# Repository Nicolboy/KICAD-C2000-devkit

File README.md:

# KICAD-C2000-devkit

- **56/56** — connector pins identical between the F280037 and F28P551
  devkits, fully interchangeable on the same shield
- **100% generated** — pin spec lives in Markdown, not in KiCad; a script
  derives the symbols and schematics from it, so GPIO/pin uniqueness and
  measurement-trace grounding are enforced rules, not just documentation
- Devkit B PCB **routed 100% on 4 layers**, DRC clean

Carrier boards for a TMS320 C2000 digital power-converter controller,
supervised by an ESP32-C6 for Wi-Fi and FOTA updates, designed in KiCad 10.

Shield d'isolation et cartes devkit pour TMS320 C2000, conçus sous KiCad 10.
Le brochage est décrit en Markdown, les symboles et les projets KiCad en sont
**générés** — le document reste la source de vérité, pas le schéma.

Cible : une commande numérique de convertisseur de puissance isolé, pilotée par
un C2000 et supervisée par un ESP32-C6 pour le Wi-Fi et la mise à jour FOTA.

---

## Architecture — quatre cartes, une barrière

| Carte | Rôle |
|---|---|
| **Puissance** | Conversion, barrière d'isolation, isolateurs (AMC0311S, AMC0300R, ISO7710, DPC817), shunts en connexion Kelvin, régulateurs |
| **Shield** | Support mécanique des deux devkits, adaptation de brochage, conditionnement analogique, protections. **Aucun composant isolé** |
| **Devkit C2000** | MCU, deux LDO 3,3 V, JTAG, bouton reset, LED, cavalier de boot |
| **Devkit ESP32** | Wi-Fi, hôte FOTA, écran OLED en SPI |

L'isolation est entièrement confinée à la carte de puissance. Le shield ne fait
que du conditionnement côté froid : c'est ce qui permet de le fabriquer en
2 couches à la maison sans se poser de question de ligne de fuite.

Liaison shield ↔ puissance : quatre nappes 2 × 8 à **alternance signal / masse
stricte 1:1**, aucune alimentation dedans. Le +5 V passe par un connecteur
séparé — les 500 mA de la commande n'ont pas à partager leur retour avec les
masses de référence des voies ADC.

---

## Le point de conception le plus notable

**Le connecteur est identique à 100 % entre le F280037 et le F28P551**, 56
positions sur 56. Les deux devkits sont interchangeables sur le shield.

Ce n'est pas une coïncidence, c'est le résultat d'un arbitrage : les LED ont été
délibérément posées sur les **entrées/sorties non communes** aux deux boîtiers,
pour que toutes les broches qui traversent le connecteur, elles, soient
communes.

---

## Le brochage est du code

Le fichier [`doc/spec-devkit.md`](doc/spec-devkit.md) fait autorité. Les
symboles KiCad, les schémas et les vérifications en découlent par génération —
on ne modifie jamais un `.kicad_sym` à la main.

```
doc/spec-devkit.md            source de vérité, relue par un humain
        │
        ├── gen_symbole_mcu.py   → build/C2000_MCU_LQFP64.kicad_sym
        │                          (dimensionne le symbole depuis les noms)
        │
        └── gen_devkit.py        → devkit_A_F280037.*  devkit_B_F28P551.*
              ▲                    kicad_gen.py — primitives communes
              │
            src/*.kicad_sch        schémas source des devkits, versionnés

shield.*                       édité à la main dans KiCad — pas généré
```

L'intérêt n'est pas le gain de temps, c'est que **les règles de conception
deviennent exécutables**. Les générateurs vérifient ce que le document promet :
unicité des broches et des GPIO, masse de part et d'autre des voies de mesure de
courant, présence des réserves. Une divergence entre l'intention et le schéma
est une erreur de script, pas un oubli qu'on découvre au routage.

`gen_symbole_mcu.py` dimensionne par exemple le corps du symbole à partir de la
longueur réelle du nom de broche le plus long, pour que les textes des quatre
faces ne se croisent jamais — plutôt qu'une taille choisie à l'œil qui casse au
premier nom un peu long.

Les schémas ne contiennent d'ailleurs **aucun fil** : toute la connectivité
passe par des étiquettes globales posées sur le point de connexion de chaque
broche. C'est ce qui permet d'ajouter un composant par script sans rien router.

---

## Concevoir avec un agent

Une part inhabituelle du travail est faite par un agent : lire les datasheets,
en extraire les contraintes, écrire la spécification, générer les symboles,
poser les composants et choisir les boîtiers. **Le placement et le routage
restent manuels** — ils encodent des choix que rien ne devine sur une chaîne de
mesure de courant.

[`doc/methode-kicad-claude.md`](doc/methode-kicad-claude.md) documente cette
façon de travailler : le partage des rôles, le déroulé d'une séance, et surtout
les pièges de format rencontrés — chacun avec sa signature, parce que KiCad
répond « échec du chargement » et rien de plus quand un fichier est malformé.

---

## Projets KiCad

Trois, pas un de plus.

| Projet | Contenu |
|---|---|
| `shield.*` | Shield, connecteurs devkit 2 × 28, quatre nappes, ESP32-C6 |
| `devkit_A_F280037.*` | Devkit TMS320F280037CSPM |
| `devkit_B_F28P551.*` | Devkit TMS320F28P551SG5PM |

---

## Reproduire

KiCad 10 et Python 3.12 requis. `kicad-cli` doit être dans le `PATH`.

```bash
python gen_symbole_mcu.py -o build/     # symboles MCU
python gen_devkit.py --force            # les deux projets devkit

kicad-cli sch erc --exit-code-violations <projet>.kicad_sch
kicad-cli pcb drc --exit-code-violations <projet>.kicad_pcb
```

`shield.*` n'apparaît pas ici : il est édité à la main et ne se régénère pas.
Les schémas de devkit produits à la racine sont en revanche **jetables** — toute
retouche manuelle y est perdue au prochain `--force`. Ce qui doit survivre se
modifie dans `src/` ou dans le générateur.

Chaque carte existe en **deux versions de fabrication** : 2 couches gravées à
la maison — pistes 1 mm, vias 2 mm, perçage 0,8 mm — pour itérer vite sur la
mécanique, et 4 couches en fabrication externe, avec plan de masse continu sous
la zone analogique. Même schéma, même brochage, seul le PCB change.

---

## État d'avancement

Travail en cours, et le dire plutôt que de le masquer :

- **Devkit B (F28P551)** — **PCB routé à 100 %** (24 empreintes, DRC à 0
  violation). Les deux connecteurs 2 × 28 portent désormais une sérigraphie
  par broche — canal ADC réel, GPIO, rôle de bus générique (`I2C_CK`/`DT`,
  `SPI_CK`/`DO`/`DI`/`CS`...) et alimentations, plutôt que les noms
  spécialisés du schéma (`Vin`, `I_SHUNT1_CMP`...), pour que le connecteur se
  lise seul. L'ERC du schéma reste à 41 violations, de la même famille que
  les autres projets (pins de réserve non pilotées).
- **Devkit A (F280037)** — PCB **peuplé** (27 empreintes posées depuis le
  schéma) mais pas encore routé : 106 pastilles non connectées au DRC.
- **Shield** — connecteurs posés, alimentations câblées avec `PWR_FLAG` par
  net. Le routage des signaux n'est pas fait : il demande des choix de
  conception qui n'ont pas leur place dans un générateur. D'où les 108
  violations d'ERC (`pin_not_connected` attendus). PCB non routé.
- **Carte de puissance** — spécifiée dans `doc/`, pas encore dessinée.

Les points laissés ouverts — caractéristiques de sortie des AMC, courant
d'entrée du REFIN, choix de VREFHI — sont listés en fin de
[`doc/decisions.md`](doc/decisions.md). Ils attendent une lecture de datasheet,
pas une estimation.

---

## Décisions à ne pas défaire

Certains choix ressemblent à des inefficacités sans en être. Les treize sont
documentés dans [`doc/decisions.md`](doc/decisions.md), chacun avec sa raison et
ce qui casse si on le défait — entre autres :

- Les **PWM3 et PWM4 restent en réserve et restent des PWM** : ce sont les deux
  seules paires complémentaires HRPWM avec temps mort matériel disponibles.
- Chaque shunt sort **deux fois**, `_MES` filtré et `_CMP` direct. Le chemin
  comparateur attaque le CMPSS sans filtre anti-repliement : pas de retard sur
  le déclenchement de la Trip Zone, et un défaut du filtre ne désarme pas la
  protection.
- Les **16 voies ADC sortent toutes** pour 9 nécessaires, les 5 libres étant
  câblées jusqu'aux réserves de nappe. Une voie ajoutée plus tard se raccorde
  sans retoucher une seule carte.

---

## Licence

[CERN-OHL-S v2](LICENSE) — CERN Open Hardware Licence, fortement réciproque.

Tu peux étudier, modifier, fabriquer et distribuer ce matériel. En contrepartie,
si tu distribues un produit fondé dessus, ou une version modifiée, tu dois
publier les sources correspondantes sous la même licence.

C'est la licence de référence du matériel libre, l'équivalent de la GPL côté
logiciel. Si tu préfères une réciprocité limitée à la carte elle-même, ou pas de
réciprocité du tout, les variantes CERN-OHL-W et CERN-OHL-P existent.

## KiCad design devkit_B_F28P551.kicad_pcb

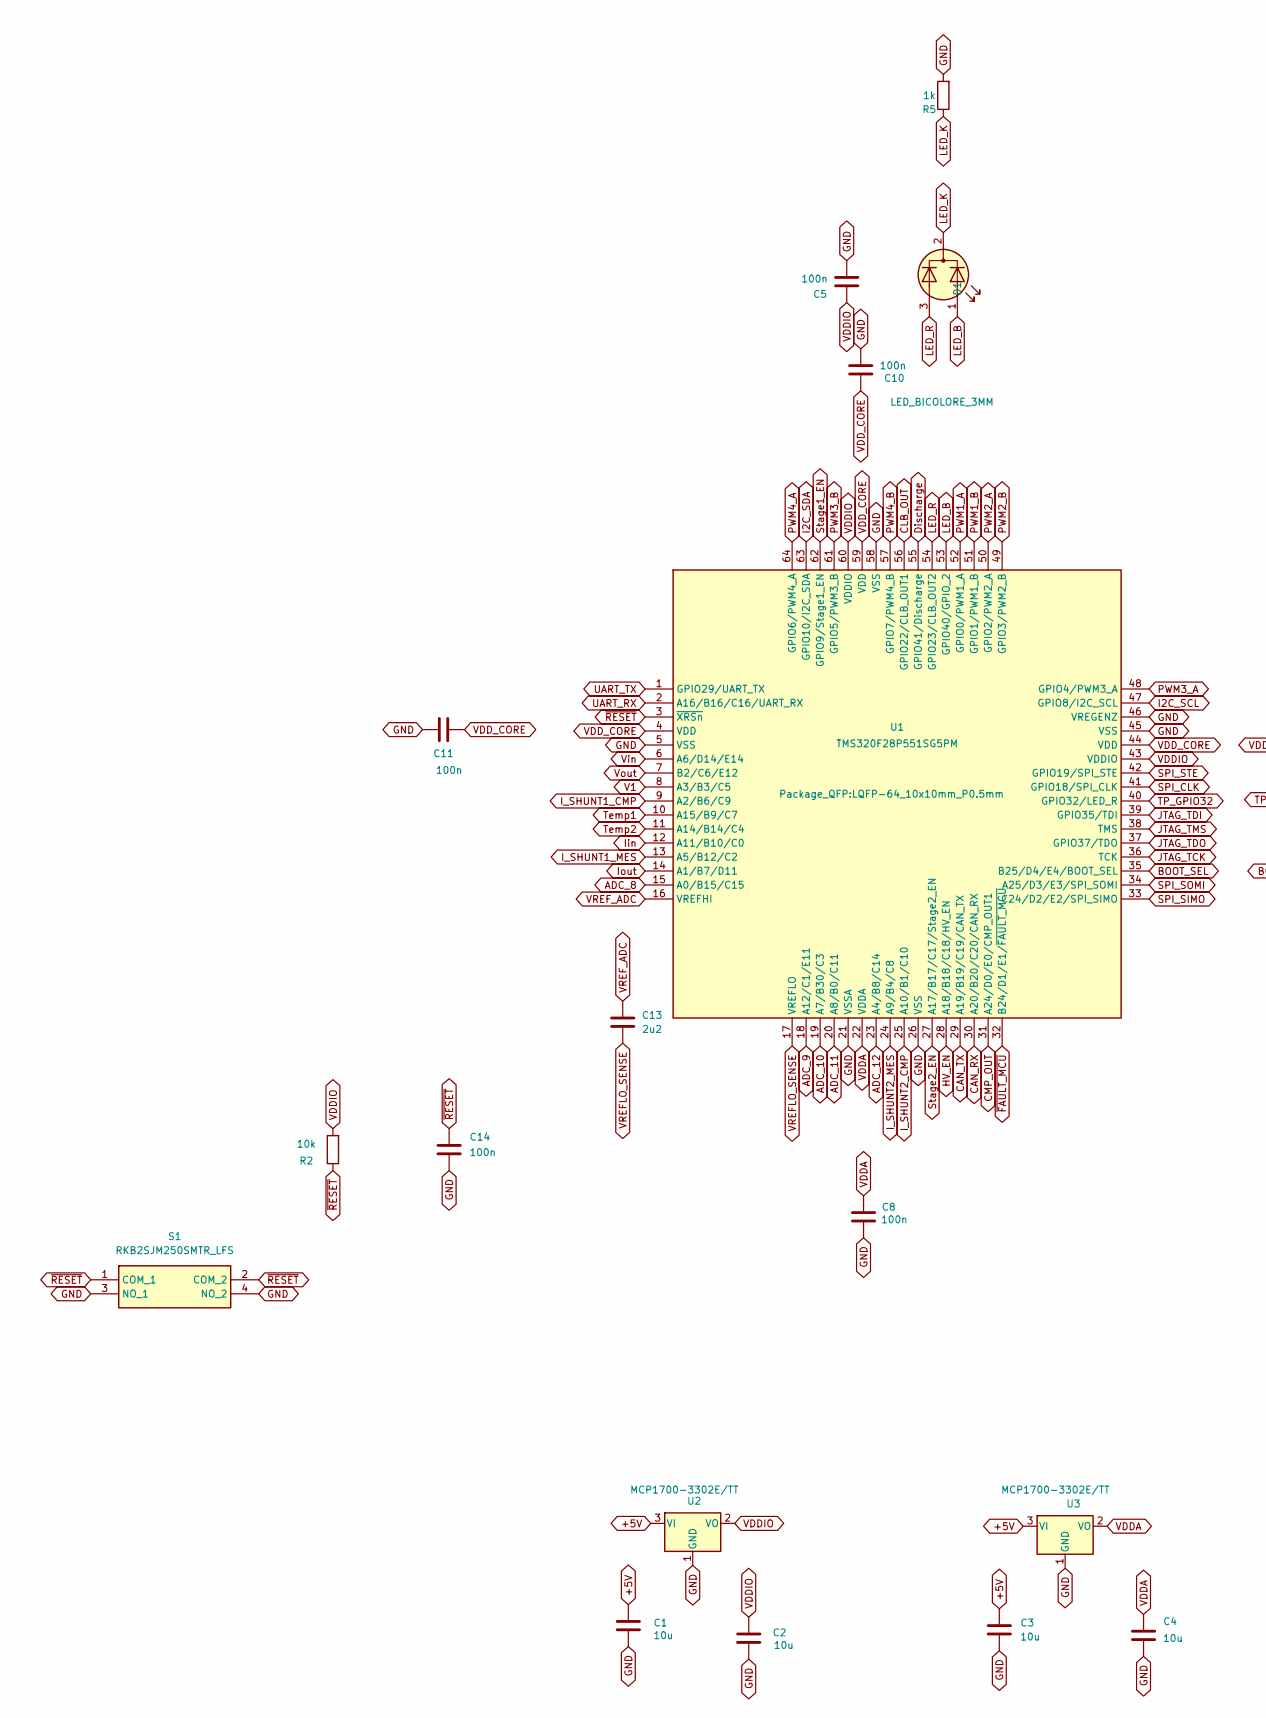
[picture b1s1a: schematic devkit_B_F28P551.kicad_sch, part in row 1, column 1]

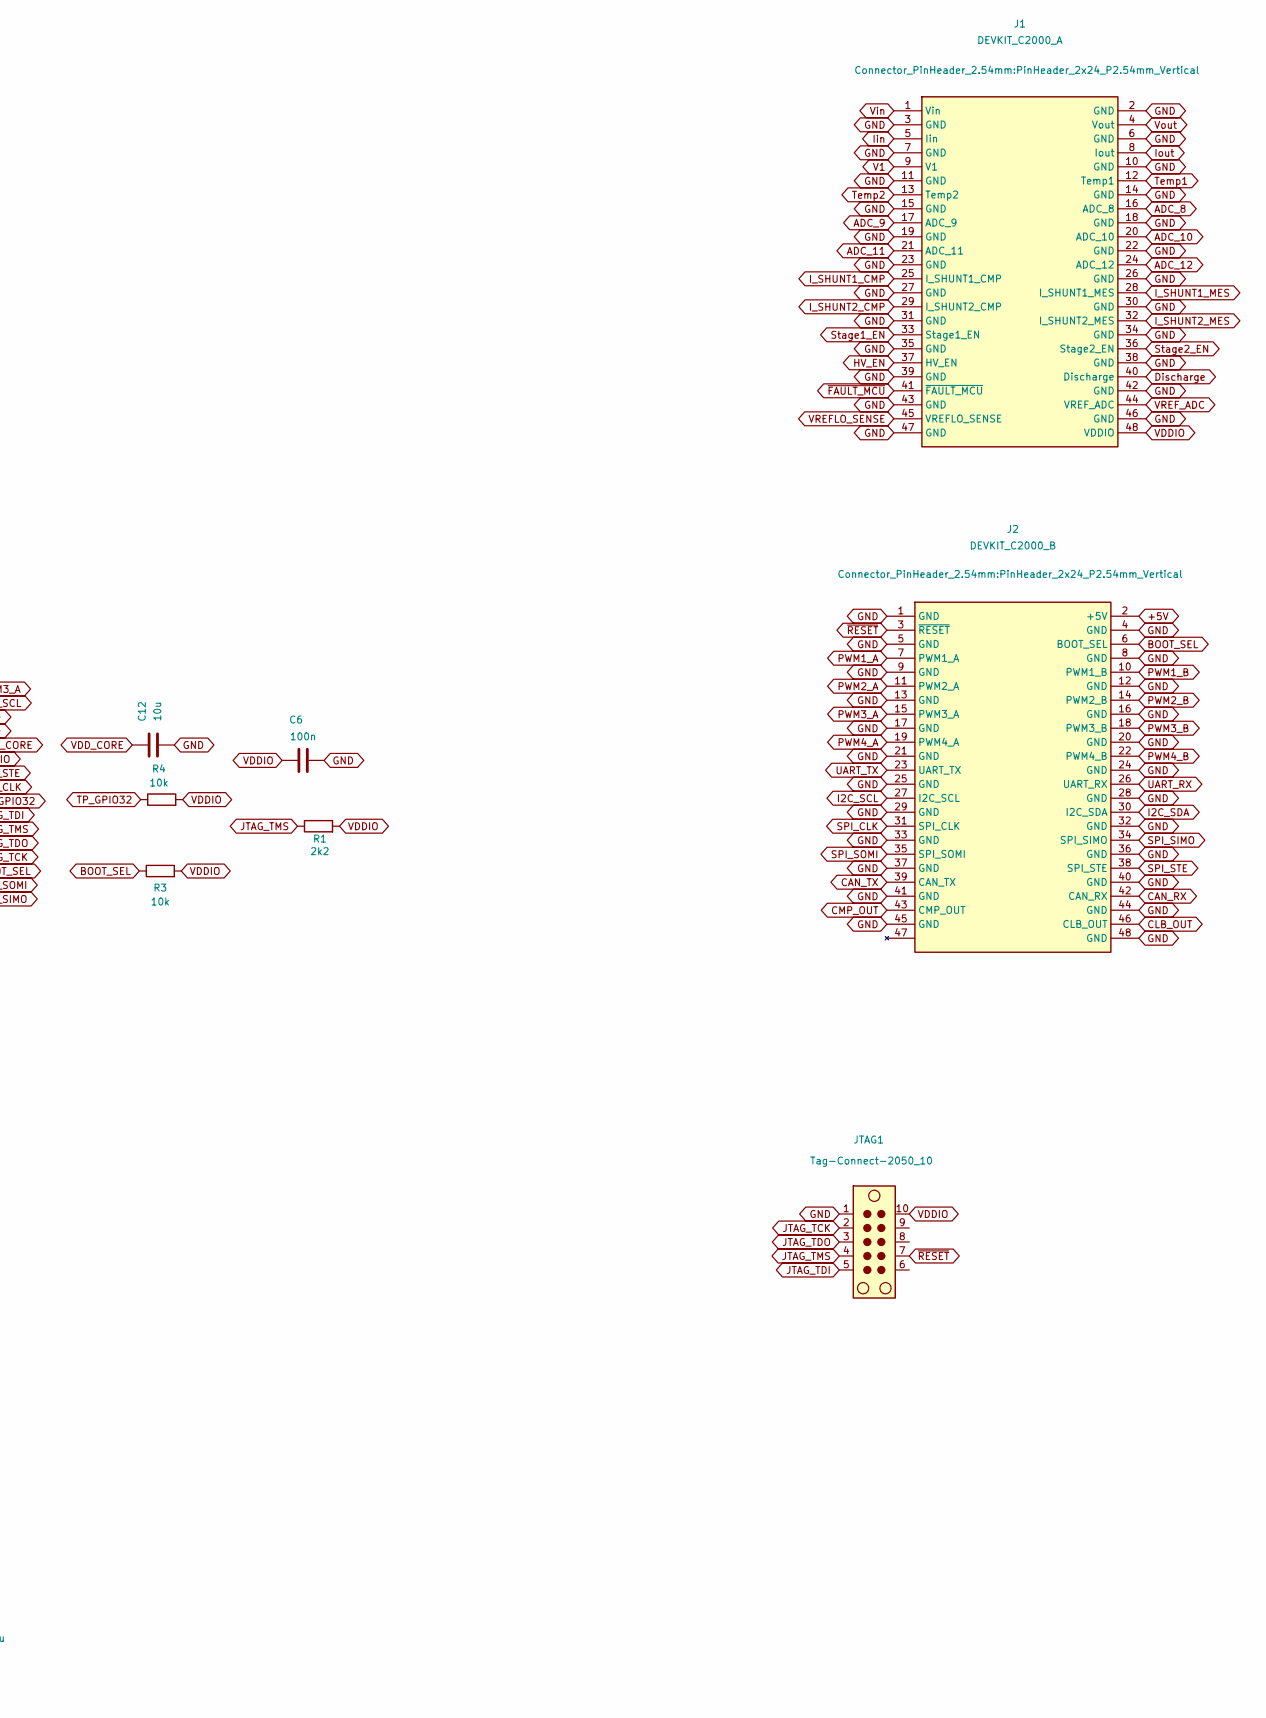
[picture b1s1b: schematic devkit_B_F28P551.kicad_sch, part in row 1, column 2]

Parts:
C1, C2, C3, C4, C12: 10u; C_0805_2012Metric
C5, C6, C8, C10, C11, C14: 100n; C_0805_2012Metric
C13: 2u2; C_0805_2012Metric
D1: LED_BICOLORE_3MM; LED_D3.0mm-3
J1: DEVKIT_C2000_A; PinHeader_2x24_P2.54mm_Vertical
J2: DEVKIT_C2000_B; PinHeader_2x24_P2.54mm_Vertical
JTAG1: Tag-Connect-2050_10; Tag-Connect_TC2050-IDC-NL_2x05_P1.27mm_Vertical
R1: 2k2; R_0805_2012Metric
R2, R3, R4: 10k; R_0805_2012Metric
R5: 1k; R_0805_2012Metric
S1: RKB2SJM250SMTR_LFS; RKB2SJM250SMTRLFS; Mouser Part Number 611-RKB2SJM250SMTRLF
U1: TMS320F28P551SG5PM; LQFP-64_10x10mm_P0.5mm
U2, U3: MCP1700-3302E/TT; SOT-23

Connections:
+5V: C1.1, C3.1, J2.2 (+5V), U2.3 (VI), U3.3 (VI)
ADC_8: J1.16 (ADC_8), U1.15 (A0/B15/C15)
ADC_9: J1.17 (ADC_9), U1.18 (A12/C1/E11)
ADC_10: J1.20 (ADC_10), U1.19 (A7/B30/C3)
ADC_11: J1.21 (ADC_11), U1.20 (A8/B0/C11)
ADC_12: J1.24 (ADC_12), U1.23 (A4/B8/C14)
BOOT_SEL: J2.6 (BOOT_SEL), R3.1, U1.35 (B25/D4/E4/BOOT_SEL)
CAN_RX: J2.42 (CAN_RX), U1.30 (A20/B20/C20/CAN_RX)
CAN_TX: J2.39 (CAN_TX), U1.29 (A19/B19/C19/CAN_TX)
CLB_OUT: J2.46 (CLB_OUT), U1.56 (GPIO22/CLB_OUT1)
CMP_OUT: J2.43 (CMP_OUT), U1.31 (A24/D0/E0/CMP_OUT1)
Discharge: J1.40 (Discharge), U1.55 (GPIO41/Discharge)
GND: C1.2, C2.2, C3.2, C4.2, C5.2, C6.2, C8.2, C10.2, C11.2, C12.2, C14.2, J1.2 (GND), J1.3 (GND), J1.6 (GND), J1.7 (GND), J1.10 (GND), J1.11 (GND), J1.14 (GND), J1.15 (GND), J1.18 (GND), J1.19 (GND), J1.22 (GND), J1.23 (GND), J1.26 (GND), J1.27 (GND), J1.30 (GND), J1.31 (GND), J1.34 (GND), J1.35 (GND), J1.38 (GND), J1.39 (GND), J1.42 (GND), J1.43 (GND), J1.46 (GND), J1.47 (GND), J2.1 (GND), J2.4 (GND), J2.5 (GND), J2.8 (GND), J2.9 (GND), J2.12 (GND), J2.13 (GND), J2.16 (GND), J2.17 (GND), J2.20 (GND), J2.21 (GND), J2.24 (GND), J2.25 (GND), J2.28 (GND), J2.29 (GND), J2.32 (GND), J2.33 (GND), J2.36 (GND), J2.37 (GND), J2.40 (GND), J2.41 (GND), J2.44 (GND), J2.45 (GND), J2.48 (GND), JTAG1.1, R5.2, S1.3 (NO_1), S1.4 (NO_2), U1.5 (VSS), U1.21 (VSSA), U1.26 (VSS), U1.45 (VSS), U1.46 (VREGENZ), U1.58 (VSS), U2.1 (GND), U3.1 (GND)
HV_EN: J1.37 (HV_EN), U1.28 (A18/B18/C18/HV_EN)
I2C_SCL: J2.27 (I2C_SCL), U1.47 (GPIO8/I2C_SCL)
I2C_SDA: J2.30 (I2C_SDA), U1.63 (GPIO10/I2C_SDA)
I_SHUNT1_CMP: J1.25 (I_SHUNT1_CMP), U1.9 (A2/B6/C9)
I_SHUNT1_MES: J1.28 (I_SHUNT1_MES), U1.13 (A5/B12/C2)
I_SHUNT2_CMP: J1.29 (I_SHUNT2_CMP), U1.25 (A10/B1/C10)
I_SHUNT2_MES: J1.32 (I_SHUNT2_MES), U1.24 (A9/B4/C8)
Iin: J1.5 (Iin), U1.12 (A11/B10/C0)
Iout: J1.8 (Iout), U1.14 (A1/B7/D11)
JTAG_TCK: JTAG1.2, U1.36 (TCK)
JTAG_TDI: JTAG1.5, U1.39 (GPIO35/TDI)
JTAG_TDO: JTAG1.3, U1.37 (GPIO37/TDO)
JTAG_TMS: JTAG1.4, R1.1, U1.38 (TMS)
LED_B: D1.1 (A1), U1.53 (GPIO40/GPIO_2)
LED_K: D1.2 (K), R5.1
LED_R: D1.3 (A2), U1.54 (GPIO23/CLB_OUT2)
PWM1_A: J2.7 (PWM1_A), U1.52 (GPIO0/PWM1_A)
PWM1_B: J2.10 (PWM1_B), U1.51 (GPIO1/PWM1_B)
PWM2_A: J2.11 (PWM2_A), U1.50 (GPIO2/PWM2_A)
PWM2_B: J2.14 (PWM2_B), U1.49 (GPIO3/PWM2_B)
PWM3_A: J2.15 (PWM3_A), U1.48 (GPIO4/PWM3_A)
PWM3_B: J2.18 (PWM3_B), U1.61 (GPIO5/PWM3_B)
PWM4_A: J2.19 (PWM4_A), U1.64 (GPIO6/PWM4_A)
PWM4_B: J2.22 (PWM4_B), U1.57 (GPIO7/PWM4_B)
SPI_CLK: J2.31 (SPI_CLK), U1.41 (GPIO18/SPI_CLK)
SPI_SIMO: J2.34 (SPI_SIMO), U1.33 (C24/D2/E2/SPI_SIMO)
SPI_SOMI: J2.35 (SPI_SOMI), U1.34 (A25/D3/E3/SPI_SOMI)
SPI_STE: J2.38 (SPI_STE), U1.42 (GPIO19/SPI_STE)
Stage1_EN: J1.33 (Stage1_EN), U1.62 (GPIO9/Stage1_EN)
Stage2_EN: J1.36 (Stage2_EN), U1.27 (A17/B17/C17/Stage2_EN)
TP_GPIO32: R4.1, U1.40 (GPIO32/LED_R)
Temp1: J1.12 (Temp1), U1.10 (A15/B9/C7)
Temp2: J1.13 (Temp2), U1.11 (A14/B14/C4)
UART_RX: J2.26 (UART_RX), U1.2 (A16/B16/C16/UART_RX)
UART_TX: J2.23 (UART_TX), U1.1 (GPIO29/UART_TX)
V1: J1.9 (V1), U1.8 (A3/B3/C5)
VDDA: C4.1, C8.1, U1.22 (VDDA), U3.2 (VO)
VDDIO: C2.1, C5.1, C6.1, J1.48 (VDDIO), JTAG1.10, R1.2, R2.2, R3.2, R4.2, U1.43 (VDDIO), U1.60 (VDDIO), U2.2 (VO)
VDD_CORE: C10.1, C11.1, C12.1, U1.4 (VDD), U1.44 (VDD), U1.59 (VDD)
VREFLO_SENSE: C13.2, J1.45 (VREFLO_SENSE), U1.17 (VREFLO)
VREF_ADC: C13.1, J1.44 (VREF_ADC), U1.16 (VREFHI)
Vin: J1.1 (Vin), U1.6 (A6/D14/E14)
Vout: J1.4 (Vout), U1.7 (B2/C6/E12)
~FAULT_MCU: J1.41 (~FAULT_MCU), U1.32 (B24/D1/E1/~FAULT_MCU)
~RESET: C14.1, J2.3 (~RESET), JTAG1.7, R2.1, S1.1 (COM_1), S1.2 (COM_2), U1.3 (~XRSn)

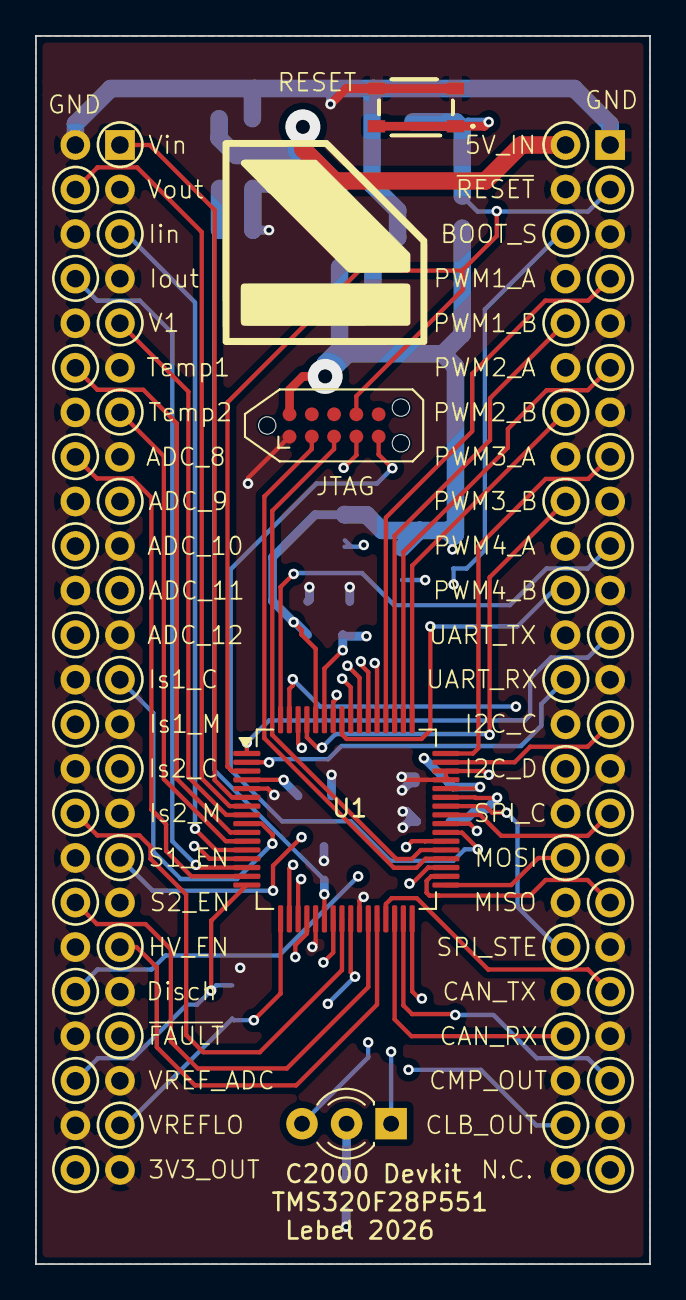
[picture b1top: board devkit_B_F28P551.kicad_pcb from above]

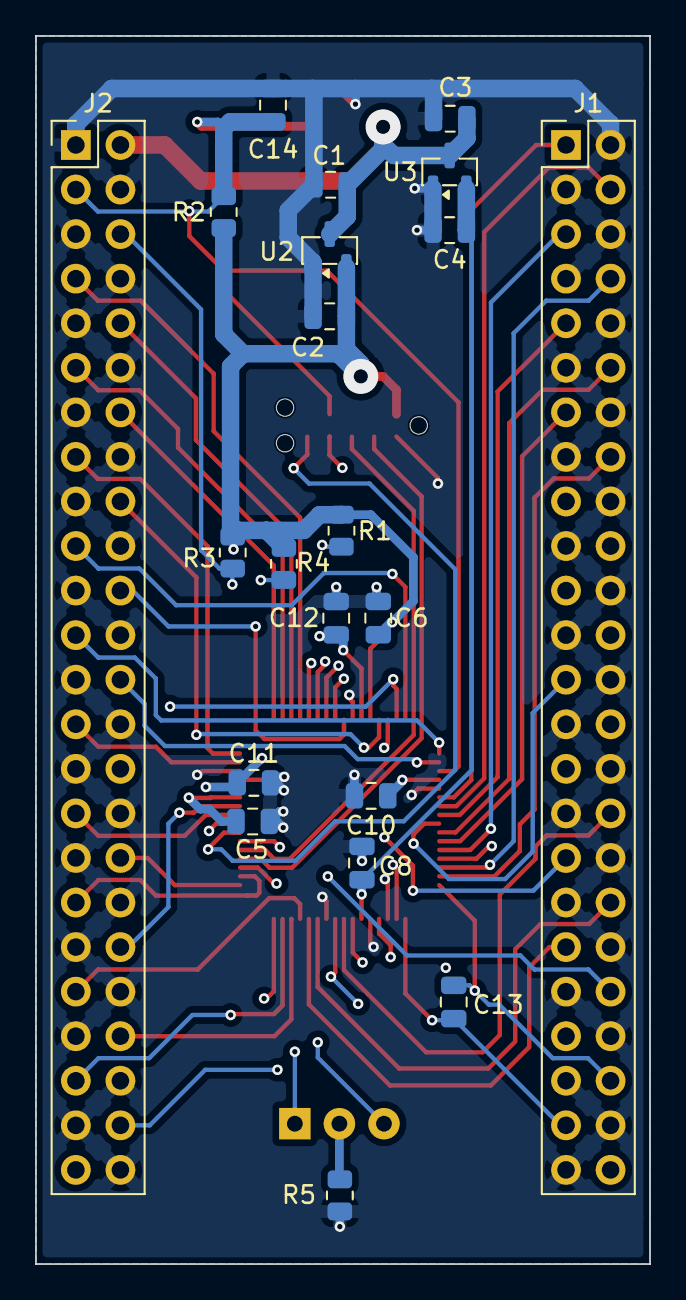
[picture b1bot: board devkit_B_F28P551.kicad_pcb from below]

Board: 4 copper layers, 35.0 x 70.0 mm, 25 parts (21 on the bottom side), 58 nets.
